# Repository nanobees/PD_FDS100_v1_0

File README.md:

# PD_FDS100_v1_0
Low Noise Photodetector Circuit Based on Thorlab's FDS100 Photodiode

This circuit is done for testing the exact wavelength of the commercial lasers we use in our lab. The commercial
photodetectors that used in our spectroscopy system is not appropriate for using with lasers so we use a Thorlabs 
FDS100 photodetector for this application. Circuit is based on the design that recommended in Thorlabs's website.
This circuit needs further testing(actually not working for mysterious reasons.) please contact me if you want to 
use this design; haltugyildirim_at_protonmail.com

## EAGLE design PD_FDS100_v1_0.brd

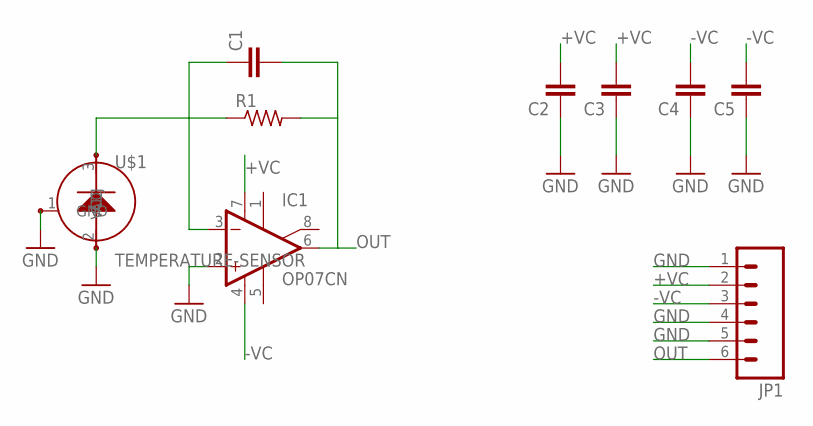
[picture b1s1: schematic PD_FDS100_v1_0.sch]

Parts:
C1, C2, C3, C4, C5: CAPPTH1; CAP-PTH-5MM
IC1: OP07CN; DIL08
JP1: M06NO_SILK; 1X06_NO_SILK
R1: R-US_0207/10; 0207/10
U$1: TEMPERATURE-SENSOR; TO-92

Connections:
+VC: C2.2, C3.2, IC1.7 (V+), JP1.2
-VC: C4.2, C5.2, IC1.4 (V-), JP1.3
GND: C2.1, C3.1, C4.1, C5.1, IC1.2 (-IN), JP1.1, JP1.4, JP1.5, U$1.1 (GND), U$1.2 (ADJ)
unnamed: C1.1, IC1.3 (+IN), R1.1, U$1.3 (VCC)
OUT: C1.2, IC1.6 (OUT), JP1.6, R1.2

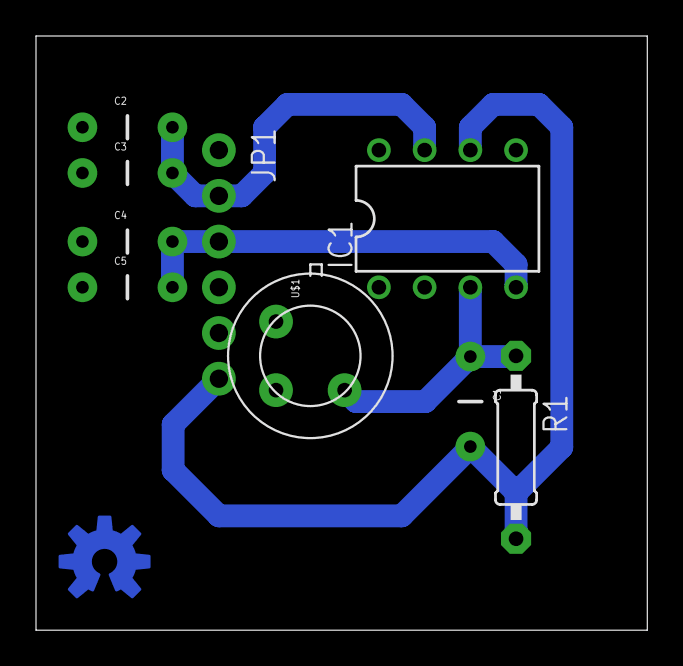
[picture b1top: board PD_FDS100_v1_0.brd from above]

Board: 2 copper layers, 34.0 x 33.0 mm, 10 parts (0 on the bottom side), 5 nets.

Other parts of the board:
U$2: OSHW-LOGO-M

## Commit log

2016-08-26 initial design files
    add initial files

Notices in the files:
parts and their libraries:
SparkFun-Capacitors: Licensing: Creative Commons ShareAlike 4.0 International - https://creativecommons.org/licenses/by-sa/4.0
